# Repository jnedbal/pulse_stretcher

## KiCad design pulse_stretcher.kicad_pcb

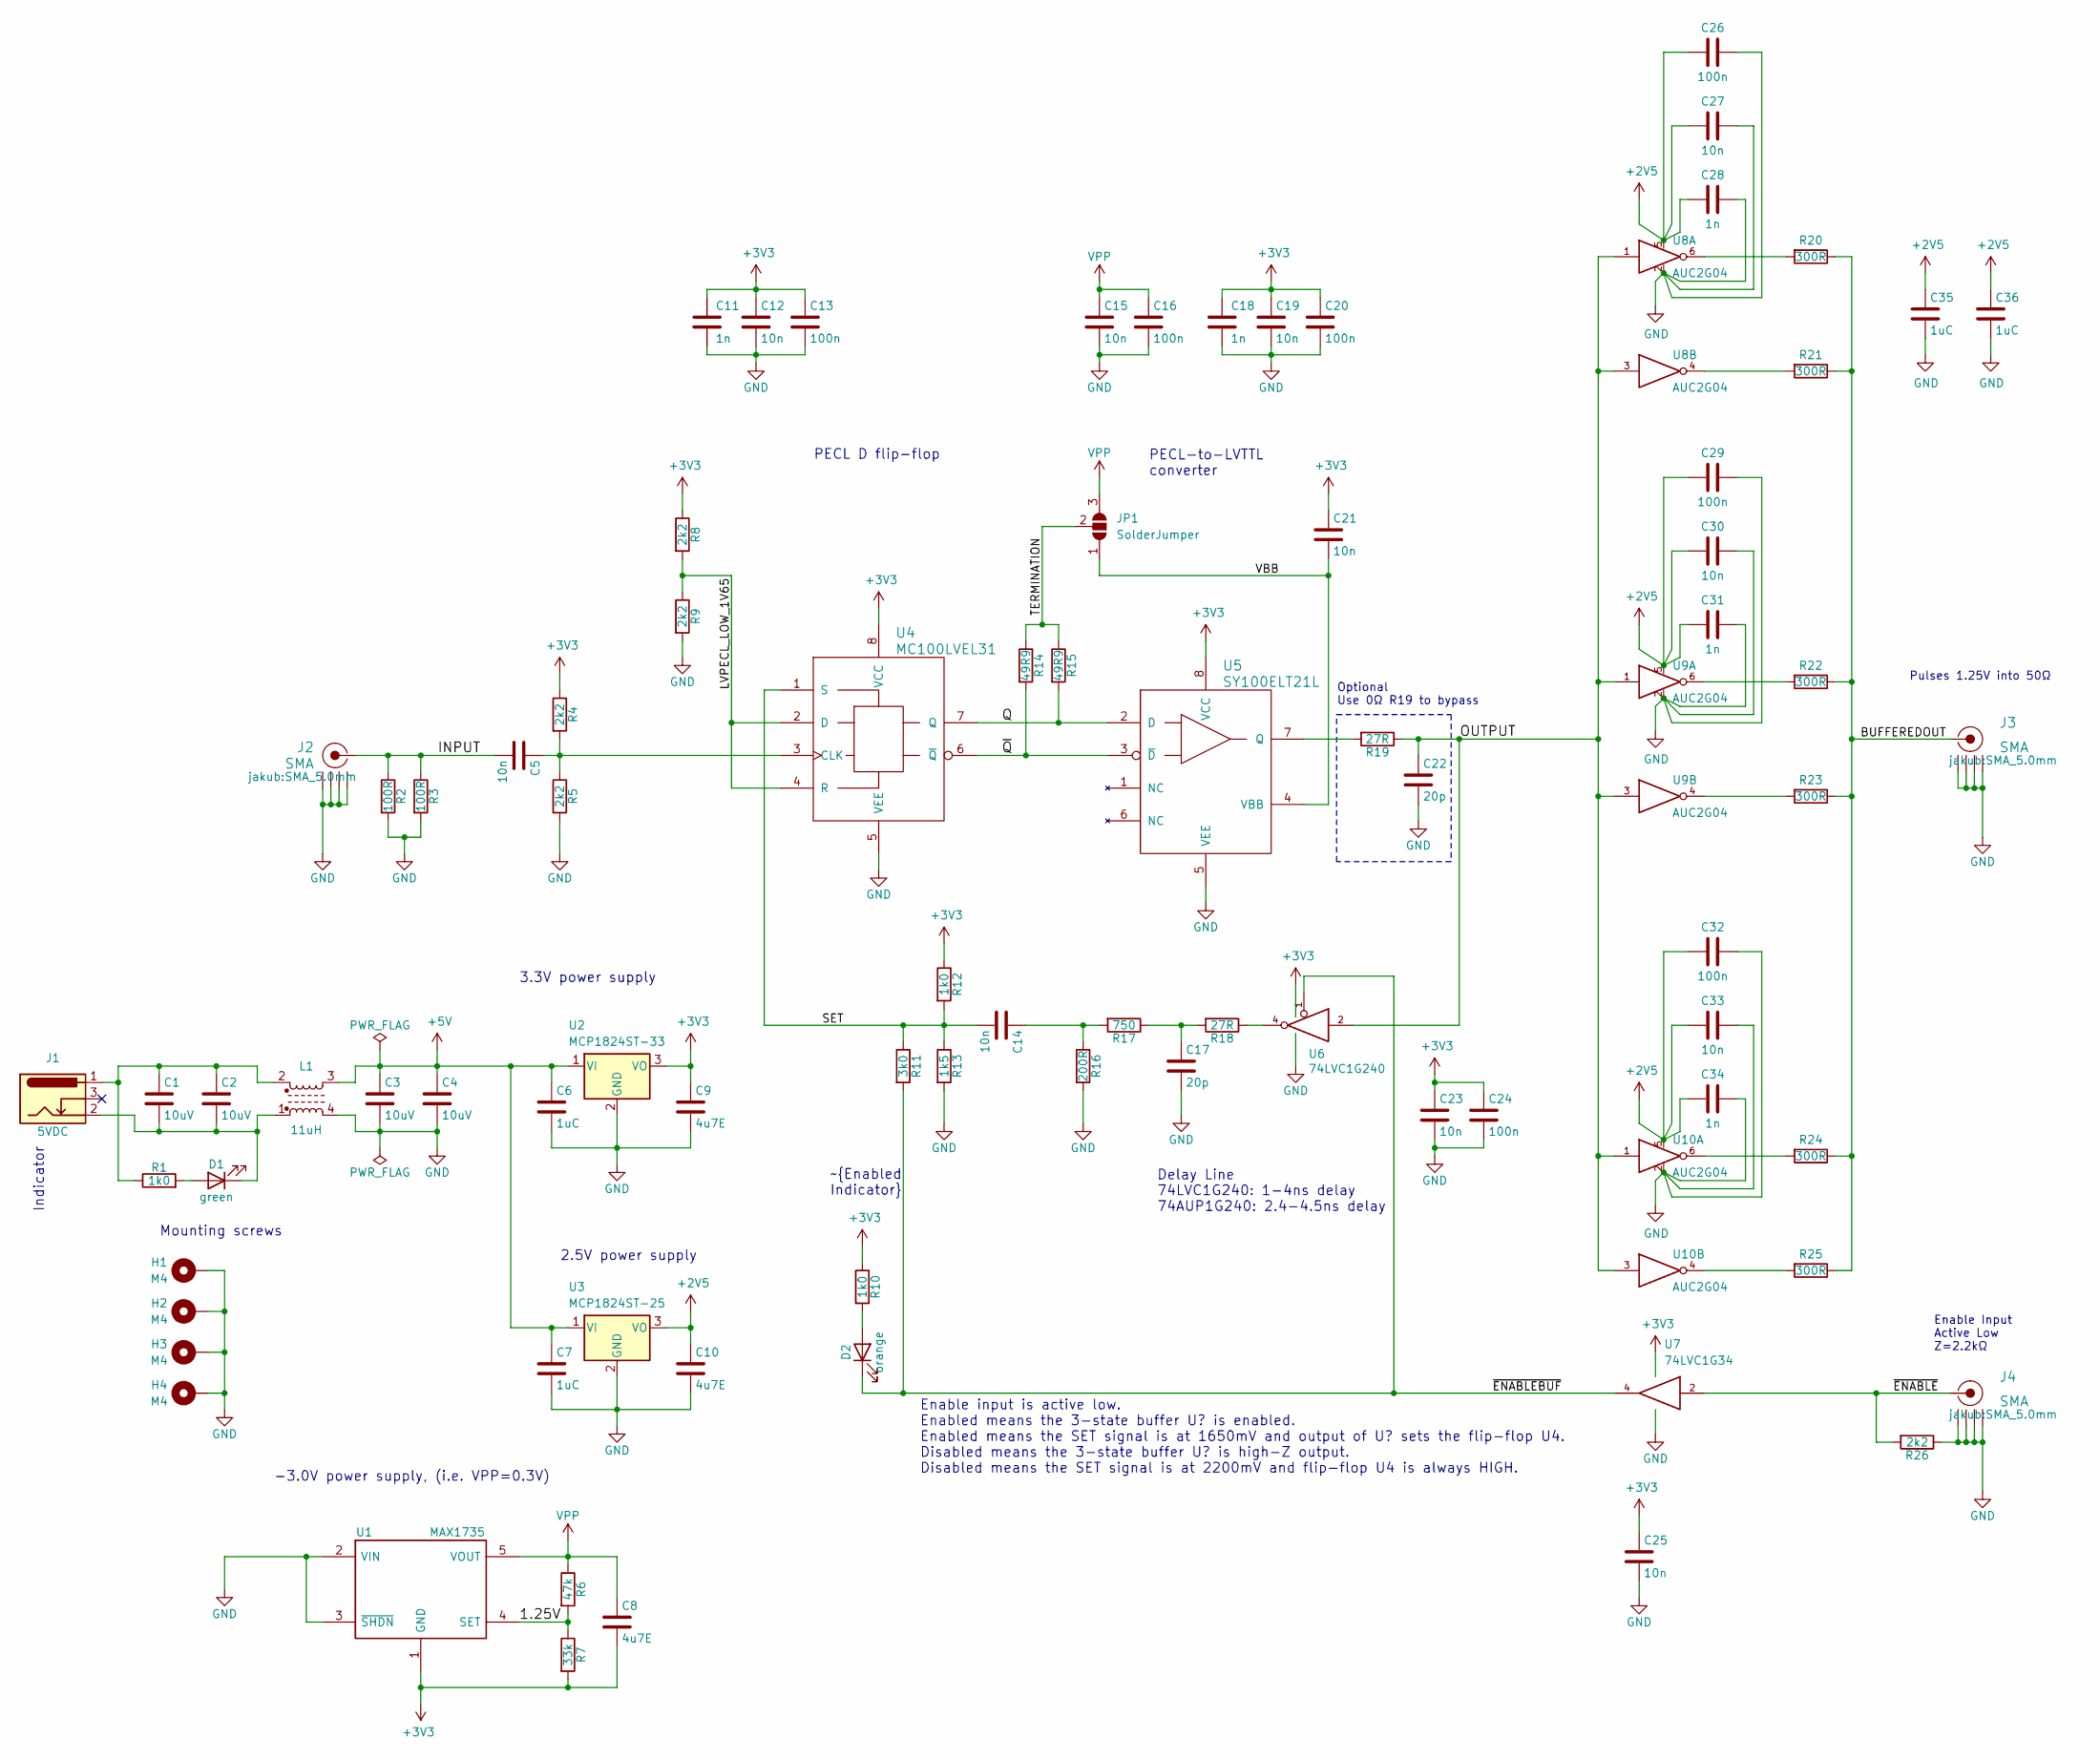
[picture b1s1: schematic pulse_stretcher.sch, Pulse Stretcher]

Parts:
C1, C2, C3, C4: 10uV; C_1206_3216Metric; Part Number GMK316AB7106KL-TR
C5, C12, C14, C15, C19, C21, C23, C25, C27, C30, C33: 10n; C_0402_1005Metric; Part Number C0402C103K5RACTU
C6, C7, C35, C36: 1uC; C_0603_1608Metric; Part Number GRM188R61E105K
C8, C9, C10: 4u7E; C_0805_2012Metric; Part Number C2012X5R1E475K125AB
C11, C18, C28, C31, C34: 1n; C_0402_1005Metric; Part Number GRM1555C1H102JA01D
C13, C16, C20, C24, C32: 100n; C_0603_1608Metric; Part Number C1608X7R1H104M080AA
C17, C22: 20p; C_0402_1005Metric; Part Number MC0402N200J500CT
C26, C29: 100n; C_0603_1608Metric; Part Number MC0603B104K500
D1: green; LED_D3.0mm; Part Number KPT-1608SECK
D2: orange; LED_D3.0mm; Part Number KPT-1608SECK
H1, H2, H3, H4: M4; MountingHole_4.3mm_M4_Pad
J1: 5VDC; BARREL_JACK; Part Number FC681465
J2, J3, J4: SMA; SMA_5.0mm; Part Number 5-1814400-1
JP1: SolderJumper; SolderJumper-3_P1.3mm_Open_RoundedPad1.0x1.5mm
L1: 11uH; DR334A; Part Number DR334A-113BE
R1, R10, R12: 1k0; R_0603_1608Metric; Part Number RC0603FR-071KL
R2, R3: 100R; R_0603_1608Metric; Part Number MCWR06X1000FTL
R4, R5, R8, R9, R26: 2k2; R_0603_1608Metric; Part Number RC0603FR-072K2L
R6: 47k; R_0603_1608Metric; Part Number MCWR06X4702FTL
R7: 33k; R_0603_1608Metric; Part Number MCWR06X3302FTL
R11: 3k0; R_0603_1608Metric; Part Number RC0603FR-073KL
R13: 1k5; R_0603_1608Metric; Part Number RC0603FR-071K5L
R14, R15: 49R9; R_0603_1608Metric; Part Number MCWR06X49R9FTL
R16: 200R; R_0603_1608Metric; Part Number RC0603FR-07200RL
R17: 750; R_0603_1608Metric; Part Number RC0603FR-07750RL
R18, R19: 27R; R_0603_1608Metric; Part Number MCWR06X27R0FTL
R20, R21, R22, R23, R24, R25: 300R; R_0402_1005Metric; Part Number MCWR04X3000FTL
U1: MAX1735; SOT-23-5; Part Number MAX1735EUK50+T
U2: MCP1824ST-33; SOT-223-3_TabPin2; Part Number MCP1824ST-3302E/DB
U3: MCP1824ST-25; SOT-223-3_TabPin2; Part Number MCP1824ST-2502E/DB
U4: MC100LVEL31; SOIC-8_3.9x4.9mm_P1.27mm; Part Number MC100LVEL31DG
U5: SY100ELT21L; SOIC-8_3.9x4.9mm_P1.27mm; Part Number SY100ELT21LZG
U6: 74LVC1G240; SOT-23-5; Part Number SN74LVC1G240DBVR
U7: 74LVC1G34; SOT-23-5; Part Number SN74LVC1G34DBVT
U8, U9, U10: AUC2G04; SOT-23-6_Handsoldering; Part Number SN74AUC2G04DBVR

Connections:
+2V5: C10.1, C26.2, C27.2, C28.1, C29.2, C30.2, C31.1, C32.2, C33.2, C34.1, C35.1, C36.1, U3.3 (VO), U8.5, U9.5, U10.5
+3V3: C8.2, C9.1, C11.1, C12.1, C13.1, C18.1, C19.1, C20.1, C21.1, C23.1, C24.1, C25.1, R4.1, R7.2, R8.1, R10.1, R12.1, U1.1 (GND), U2.3 (VO), U4.8 (VCC), U5.8 (VCC), U6.5 (VCC), U7.5 (VCC)
+5V: C3.1, C4.1, C6.1, C7.1, L1.3, U2.1 (VI), U3.1 (VI)
/1.25V: R6.2, R7.1, U1.4 (SET)
/BUFFEREDOUT: J3.1 (RF), R20.1, R21.1, R22.1, R23.1, R24.1, R25.1
/INPUT: C5.2, J2.1 (RF), R2.1, R3.1
/LVPECL_LOW_1V65: R8.2, R9.1, U4.2 (D), U4.4 (R)
/OUTPUT: C22.1, R19.1, U6.2, U8.1, U8.3, U9.1, U9.3, U10.1, U10.3
/Q: R15.2, U4.7 (Q), U5.2 (D)
/SET: C14.2, R11.1, R12.2, R13.1, U4.1 (S)
/TERMINATION: JP1.2 (C), R14.1, R15.1
/VBB: C21.2, JP1.1 (A), U5.4 (VBB)
/~ENABLE: J4.1 (RF), R26.2, U7.2
/~ENABLEBUF: D2.1 (K), R11.2, U6.1, U7.4
/~Q: R14.2, U4.6 (~Q), U5.3 (~D)
GND: C3.2, C4.2, C6.2, C7.2, C9.2, C10.2, C11.2, C12.2, C13.2, C15.2, C16.2, C17.2, C18.2, C19.2, C20.2, C22.2, C23.2, C24.2, C25.2, C26.1, C27.1, C28.2, C29.1, C30.1, C31.2, C32.1, C33.1, C34.2, C35.2, C36.2, H1.1, H2.1, H3.1, H4.1, J2.2 (GND1), J2.3 (GND2), J2.4 (GND3), J2.5 (GND4), J3.2 (GND1), J3.3 (GND2), J3.4 (GND3), J3.5 (GND4), J4.2 (GND1), J4.3 (GND2), J4.4 (GND3), J4.5 (GND4), L1.4, R2.2, R3.2, R5.2, R9.2, R13.2, R16.2, R26.1, U1.2 (VIN), U1.3 (~SHDN), U2.2 (GND), U3.2 (GND), U4.5 (VEE), U5.5 (VEE), U6.3 (GND), U7.3 (GND), U8.2, U9.2, U10.2
unnamed: C1.1, C2.1, J1.1, L1.2, R1.1
unnamed: C1.2, C2.2, D1.1 (K), J1.2, L1.1
unnamed: C5.1, R4.2, R5.1, U4.3 (CLK)
unnamed: C14.1, R16.1, R17.2
unnamed: C17.1, R17.1, R18.2
unnamed: D1.2 (A), R1.2
unnamed: D2.2 (A), R10.2
unnamed: R18.1, U6.4
unnamed: R19.2, U5.7 (Q)
unnamed: R20.2, U8.6
unnamed: R21.2, U8.4
unnamed: R22.2, U9.6
unnamed: R23.2, U9.4
unnamed: R24.2, U10.6
unnamed: R25.2, U10.4
VPP: C8.1, C15.1, C16.1, JP1.3 (B), R6.1, U1.5 (VOUT)

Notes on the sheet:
3.3V power supply
-3.0V power supply, (i.e. VPP=0.3V)
Delay Line 74LVC1G240: 1-4ns delay 74AUP1G240: 2.4-4.5ns delay
PECL D flip-flop
PECL-to-LVTTL converter
Mounting screws
Indicator
2.5V power supply
Pulses 1.25V into 50Ω
Enable input is active low. Enabled means the 3-state buffer U? is enabled. Enabled means the SET signal is at 1650mV and output of U? sets the flip-flop U4. Disabled means the 3-state buffer U? is high-Z output. Disabled means the SET signal is at 2200mV and flip-flop U4 is always HIGH.
Enable Input Active Low Z=2.2kΩ
~Enabled Indicator
Optional Use 0Ω R19 to bypass

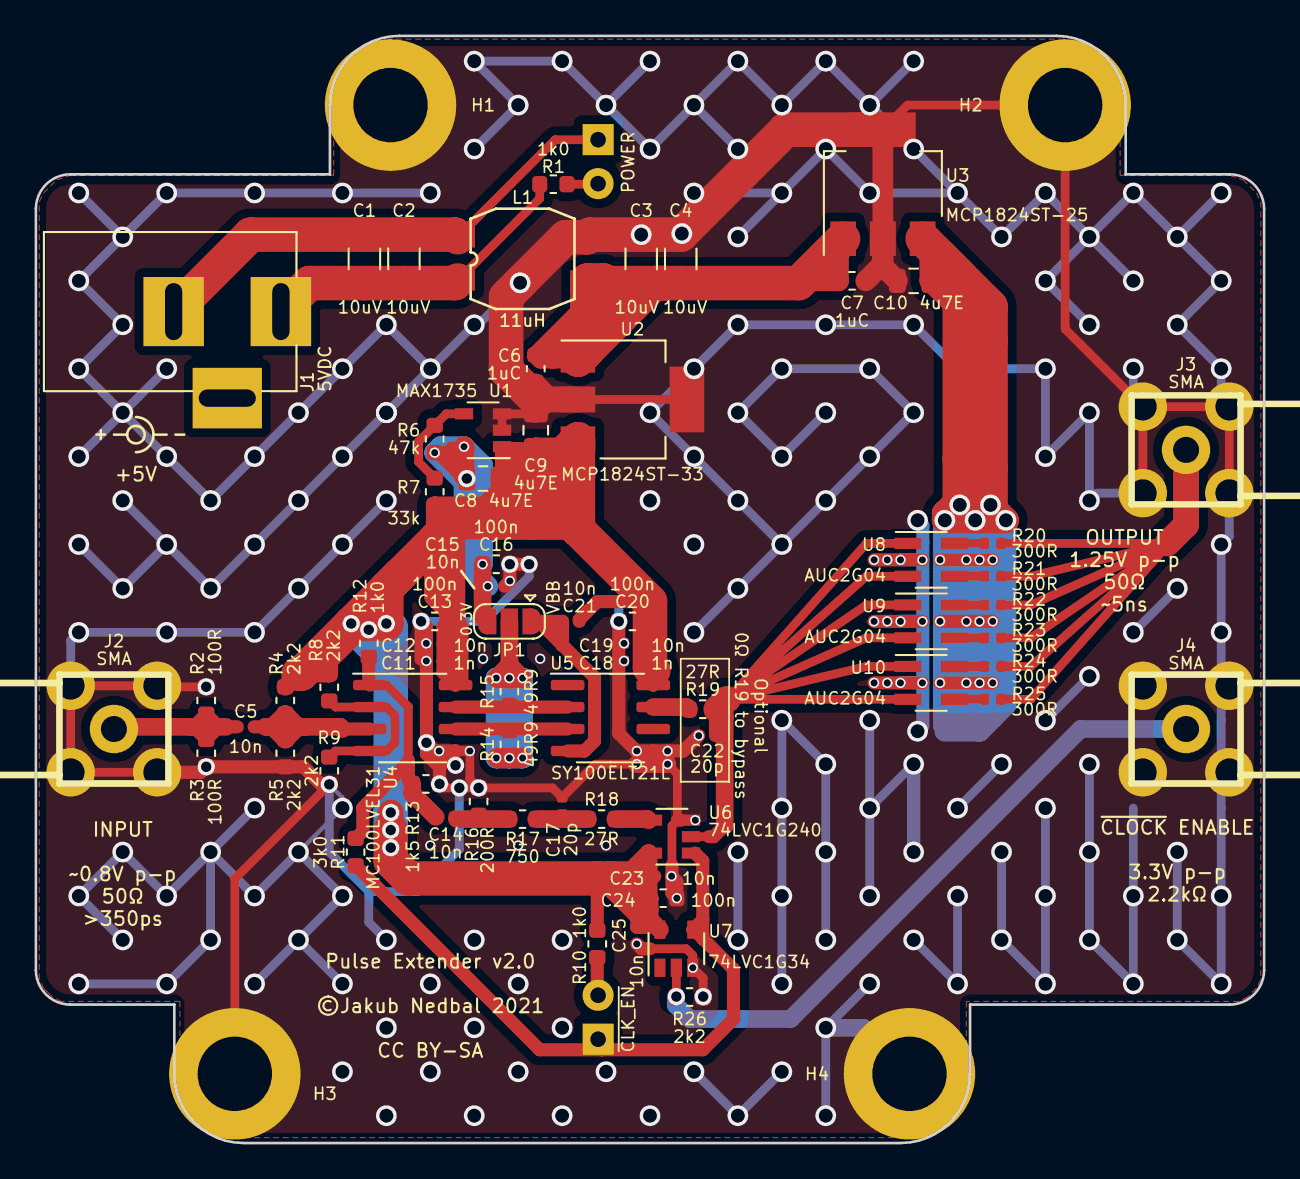
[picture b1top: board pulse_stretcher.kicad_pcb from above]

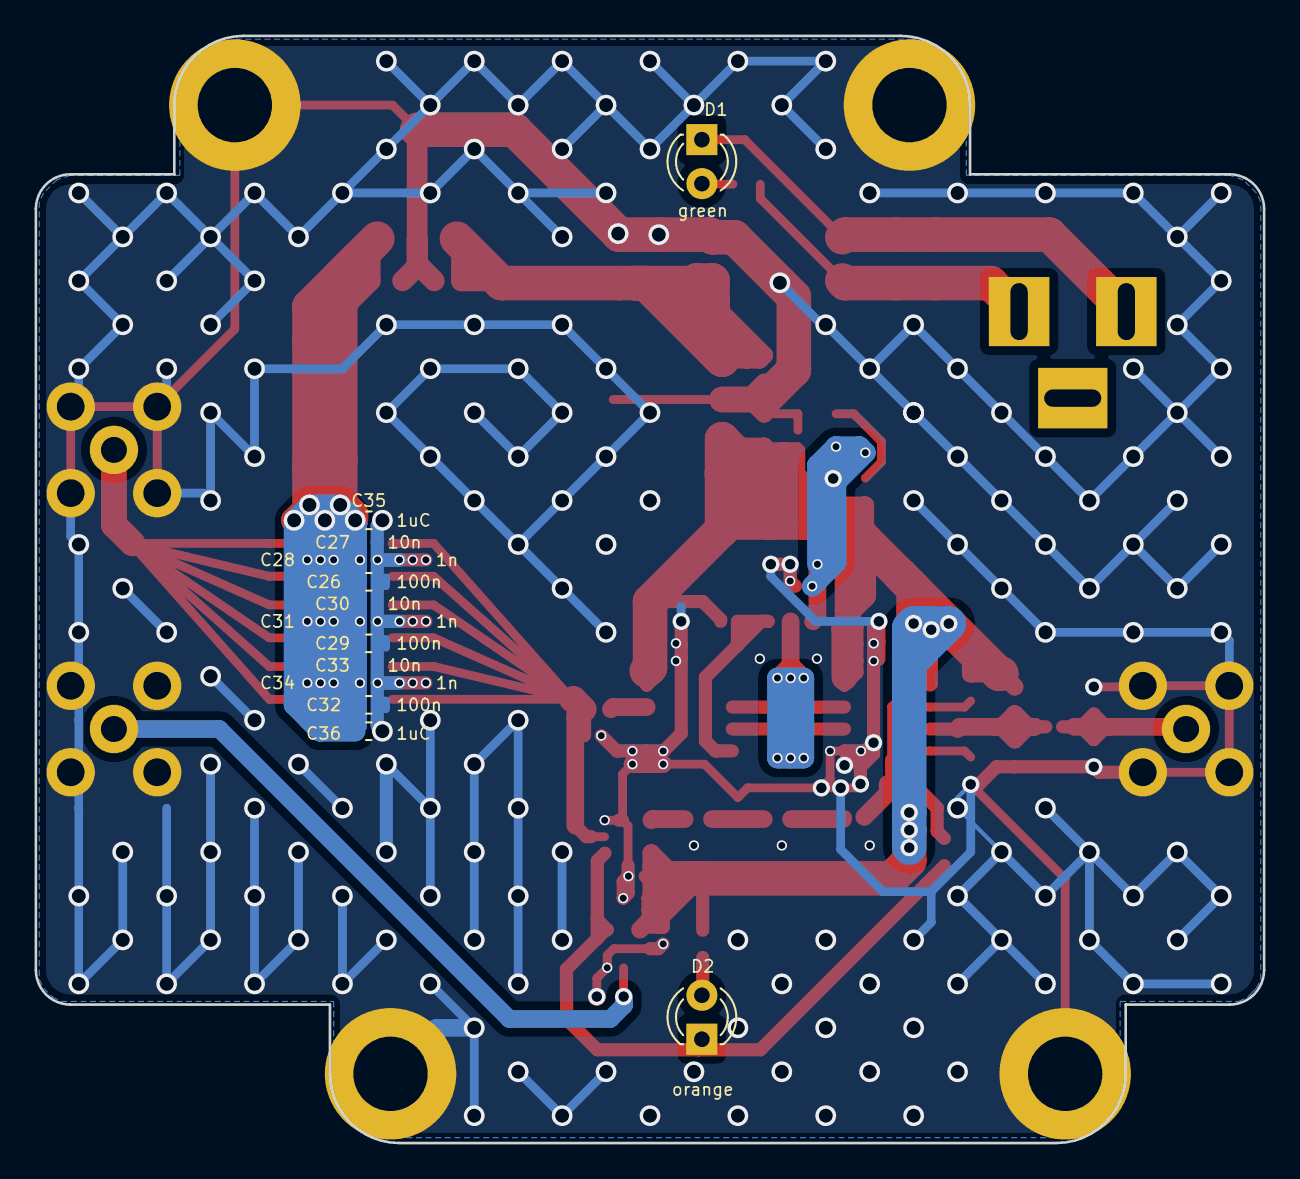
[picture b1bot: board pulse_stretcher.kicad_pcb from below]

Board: 2 copper layers, 71.0 x 64.0 mm, 84 parts (13 on the bottom side), 32 nets.

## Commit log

2021-11-09 Initial commit. Waiting on parts to check board will fit the box.
2021-11-12 Redesigned the PCB
2021-11-12 Added ~clock_enable
2021-11-12 Added comment about RC filter being optional
2021-11-15 Production run

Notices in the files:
pulse_stretcher.kicad_pcb:
©Jakub Nedbal 2021
CC BY-SA
pulse_stretcher.sch:
Creative Commons Attribution-ShareAlike 4.0 International License
This work is licensed under a
